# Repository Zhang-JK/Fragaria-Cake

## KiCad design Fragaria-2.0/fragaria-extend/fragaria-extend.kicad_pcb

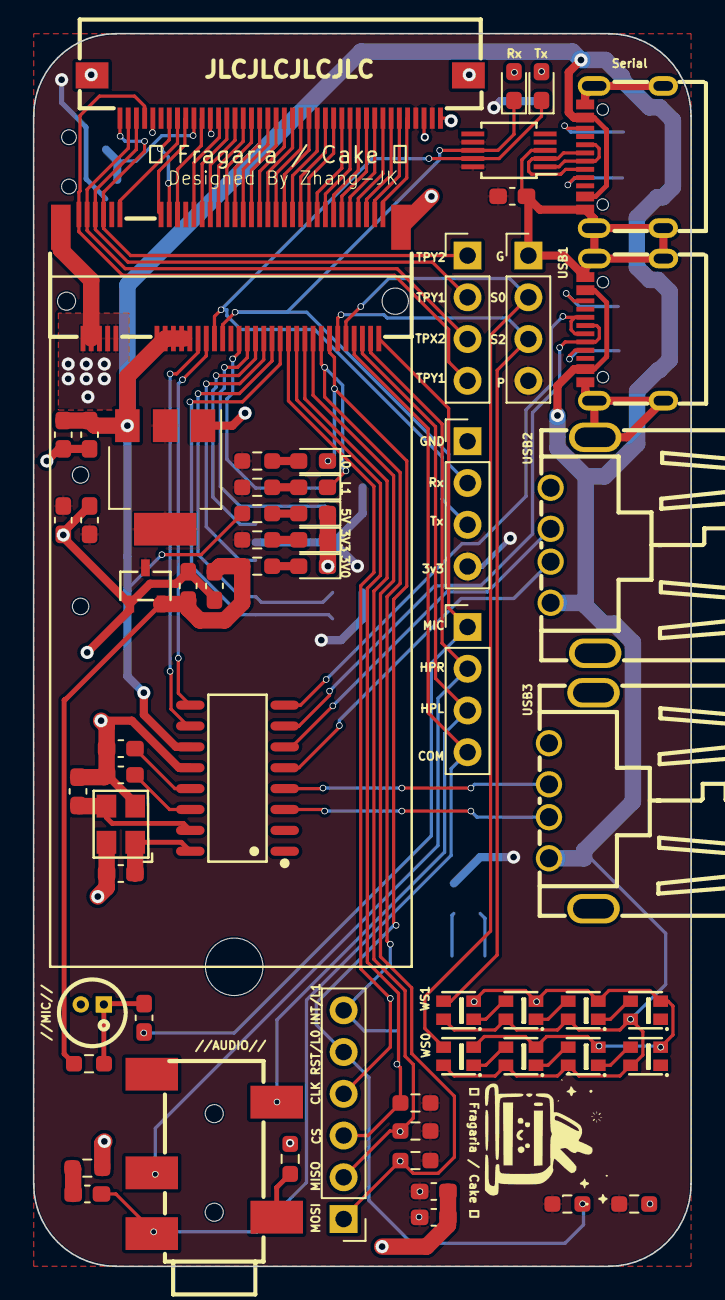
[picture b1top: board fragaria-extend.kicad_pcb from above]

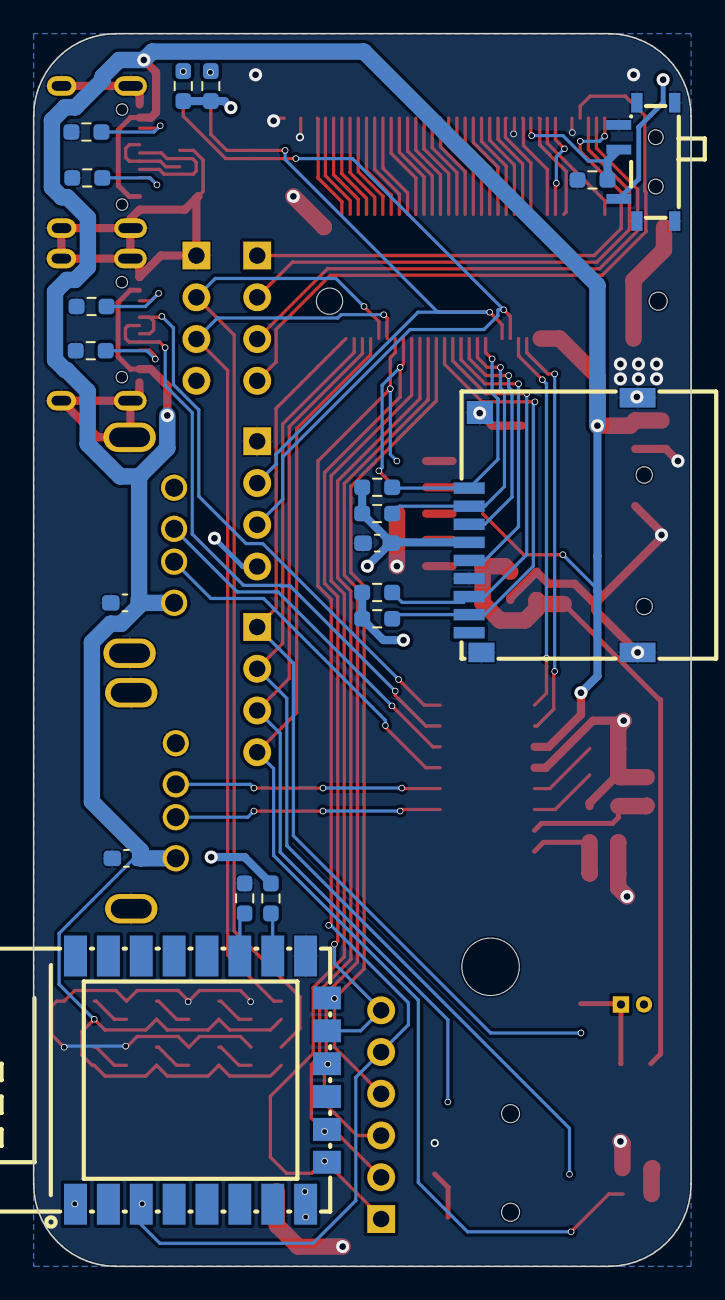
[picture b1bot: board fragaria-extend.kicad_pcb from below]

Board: 2 copper layers, 40.0 x 75.0 mm, 81 parts (19 on the bottom side), 94 nets.

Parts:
C1, C3, C5, C11, C13, C14, C16, C18, C19: 0.1uF; C_0603_1608Metric_Pad1.08x0.95mm_HandSolder
C2, C4, C6, C9, C10, C15: 10uF; C_0603_1608Metric_Pad1.08x0.95mm_HandSolder
C7, C8: 20pF; C_0603_1608Metric_Pad1.08x0.95mm_HandSolder
C17: 2.2uF; C_0603_1608Metric_Pad1.08x0.95mm_HandSolder
CN1: AS0BC21-S40BB-7H; CONN-SMD_AS0BC21-S30BB-7H
CN2: PJ-327A_5JJ; AUDIO-SMD_PJ-327A5JJ
Card1: MR01A-01211; TF-SMD_MR01A-01211
D1, D2, D3, D4: LED-R; LED_0603_1608Metric_Pad1.05x0.95mm_HandSolder
D5: LED-B; LED_0603_1608Metric_Pad1.05x0.95mm_HandSolder
D6, D7: LED-G; LED_0603_1608Metric_Pad1.05x0.95mm_HandSolder
FPC1: AFC01-S40FCA-00; FPC-SMD_P0.50-40P_FGS-XJ-H2.0
J1, J2, J4, J5: Conn_01x04; PinHeader_1x04_P2.54mm_Vertical
J3: Conn_01x06; PinHeader_1x06_P2.54mm_Vertical
LED1, LED2, LED3, LED4, LED5, LED6, LED7, LED8: WS2812B-2020; LED-SMD_4P-L2.0-W2.0-TL_WS2812B-2020
MIC1: B4012AP422-003; MIC-TH_BD4.0-P1.40-D0.3-L
R1, R2, R3, R8, R9, R10, R11: 2kΩ; R_0603_1608Metric_Pad0.98x0.95mm_HandSolder
R4, R5, R6, R7: 5.1kΩ; R_0603_1608Metric_Pad0.98x0.95mm_HandSolder
R12, R13, R14, R15, R16, R23, R24, R25, R26: 10KΩ; R_0603_1608Metric_Pad0.98x0.95mm_HandSolder
R17, R18, R19, R20: 47kΩ; R_0603_1608Metric_Pad0.98x0.95mm_HandSolder
R21: 22Ω; R_0603_1608Metric_Pad0.98x0.95mm_HandSolder
R22: 1KΩ; R_0603_1608Metric_Pad0.98x0.95mm_HandSolder
SW1: MSK12C02; SW-TH_MSK12C02
U1: XC6206P302MR_C347375; SOT-23-3_L3.0-W1.7-P0.95-LS2.9-BR
U2: AMS1117-3.3; SOT-223-3_TabPin2
U3: SL2.1A; SOP-16_L10.0-W3.9-P1.27-LS6.0-BL
U4: CH340E; MSOP-10_3x3mm_P0.5mm
U5: ESP-12F(ESP8266MOD); WIFIM-SMD_ESP-12F-ESP8266MOD
USB1, USB2: TYPE-C_16PIN_2MD(073); USB-C-SMD_TYPE-C-6PIN-2MD-073
USB4, USB5: 292303-1; USB-A-TH_USB-302-T
X1: X322512MSB4SI; OSC-SMD_4P-L3.2-W2.5-BL
locked: locked; MountingHole_3.5mm

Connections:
+3V0: C3.2, C6.2, R3.1, R14.1, U1.2 (VOUT)
+3V3: C4.1, C5.1, C11.2, C15.2, C16.2, C18.2, Card1.4 (VDD), FPC1.2, FPC1.4, J2.4, J5.4, R2.1, R8.1, R9.1, R10.1, R11.1, R12.1, R13.1, R15.1, R17.1, R18.1, R19.1, R20.1, R23.2, R24.2, R25.2, SW1.1, U1.3 (VIN), U2.2 (VO), U4.7 (VCC), U4.10 (V3), U5.8 (VCC)
+5V: C1.1, C2.1, C13.2, C14.2, CN1.20, CN1.22, CN1.24, CN1.26, CN1.28, LED1.4 (VDD), LED2.4 (VDD), LED3.4 (VDD), LED4.4 (VDD), LED5.4 (VDD), LED6.4 (VDD), LED7.4 (VDD), LED8.4 (VDD), R1.1, U2.3 (VI), U3.11 (VDD5), USB1.2 (VBUS), USB1.11 (VBUS), USB2.2 (VBUS), USB2.11 (VBUS), USB4.1 (S+), USB5.1 (S+)
/BD+: CN1.30, U3.10 (DP)
/BD-: CN1.32, U3.9 (DM)
/D+: U4.1 (UD+), USB1.6 (DP1), USB1.8 (DP2)
/D-: U4.2 (UD-), USB1.5 (DN2), USB1.7 (DN1)
/DN1: U3.7 (DM1), USB2.5 (DN2), USB2.7 (DN1)
/DN2: U3.5 (DM2), USB4.2 (D-)
/DN3: U3.3 (DM3), USB5.2 (D-)
/DP1: U3.8 (DP1), USB2.6 (DP1), USB2.8 (DP2)
/DP2: U3.6 (DP2), USB4.3 (D+)
/DP3: U3.4 (DP3), USB5.3 (D+)
/HPCOM: C19.2, CN1.68, CN2.1, J4.4
/HPL: CN1.70, CN2.4, J4.3
/HPR: CN1.72, CN2.3, J4.2
/LCD_CLK: CN1.25, FPC1.30
/LCD_D0: CN1.75, FPC1.5
/LCD_D1: CN1.73, FPC1.6
/LCD_D2: CN1.71, FPC1.7
/LCD_D3: CN1.69, FPC1.8
/LCD_D4: CN1.67, FPC1.9
/LCD_D5: CN1.65, FPC1.10
/LCD_D6: CN1.63, FPC1.11
/LCD_D7: CN1.61, FPC1.12
/LCD_D8: CN1.59, FPC1.13
/LCD_D9: CN1.57, FPC1.14
/LCD_D10: CN1.55, FPC1.15
/LCD_D11: CN1.53, FPC1.16
/LCD_D12: CN1.51, FPC1.17
/LCD_D13: CN1.49, FPC1.18
/LCD_D14: CN1.47, FPC1.19
/LCD_D15: CN1.45, FPC1.20
/LCD_D16: CN1.43, FPC1.21
/LCD_D17: CN1.41, FPC1.22
/LCD_D18: CN1.39, FPC1.23
/LCD_D19: CN1.37, FPC1.24
/LCD_D20: CN1.35, FPC1.25
/LCD_D21: CN1.33, FPC1.26
/LCD_D22: CN1.31, FPC1.27
/LCD_D23: CN1.29, FPC1.28
/LCD_DE: CN1.23, FPC1.34
/LCD_EN: FPC1.31, R26.1, SW1.2
/LCD_HSYNC: CN1.21, FPC1.32
/LCD_VSYNC: CN1.11, FPC1.33
/LED0: CN1.62, D4.1 (K), J3.5, R13.2, U5.3 (EN)
/LED1: CN1.60, D6.1 (K), J3.6, U5.21 (MOSI)
/MICIN: C17.2, CN1.74, J4.1
/SD_CLK: CN1.46, Card1.5 (CLK)
/SD_CMD: CN1.44, Card1.3 (CMD)
/SD_D0: CN1.48, Card1.7 (DAT0), R19.2
/SD_D1: CN1.50, Card1.8 (DAT1), R20.2
/SD_D2: CN1.40, Card1.1 (DAT2), R17.2
/SD_D3: CN1.42, Card1.2 (CD/DAT3), R18.2
/SPI0_CLK: CN1.52, J3.4, U5.22 (SCLK)
/SPI0_CS: CN1.54, J3.3, R23.1, U5.20 (GPIO10)
/SPI0_MISO: CN1.56, J3.2, R24.1, U5.18 (MISO)
/SPI0_MOSI: CN1.58, J3.1, R25.1, U5.17 (CS0)
/TPX1: CN1.1, FPC1.37, J1.4
/TPX2: CN1.3, FPC1.39, J1.3
/TPY1: CN1.5, FPC1.38, J1.2
/TPY2: CN1.7, FPC1.40, J1.1
/U2_RX: CN1.36, D5.1 (K), J2.2, U4.8 (TXD)
/U2_TX: CN1.34, D7.1 (K), J2.3, U4.9 (RXD)
/WS0: CN1.66, J5.2, LED2.3 (DI)
/WS1: CN1.64, J5.3, LED1.3 (DI)
/XIN: C8.2, U3.16 (XIN), X1.1 (OSC1)
/XOUT: C7.1, U3.15 (XOUT), X1.3 (OSC2)
GND: C1.2, C2.2, C3.1, C4.2, C5.2, C6.1, C7.2, C8.1, C9.2, C10.2, C11.1, C13.1, C14.1, C15.1, C16.1, C18.1, CN1.2, CN1.4, CN1.6, CN1.8, CN1.10, CN1.76, CN1.77, Card1.6 (VSS), Card1.10 (GND), Card1.11 (GND), Card1.12 (GND), Card1.13 (GND), D1.1 (K), D2.1 (K), D3.1 (K), FPC1.1, FPC1.3, FPC1.29, FPC1.36, FPC1.41, FPC1.42, J2.1, J5.1, LED1.2 (GND), LED2.2 (GND), LED3.2 (GND), LED4.2 (GND), LED5.2 (GND), LED6.2 (GND), LED7.2 (GND), LED8.2 (GND), MIC1.2 (GND), R4.2, R5.2, R6.2, R7.2, R16.1, R21.1, R22.2, R26.2, SW1.3, SW1.4, U1.1 (VSS), U2.1 (GND), U3.12 (GND), U4.3 (GND), U5.9 (GND), USB1.1 (GND), USB1.12 (GND), USB1.13 (SHELL), USB1.14 (SHELL), USB2.1 (GND), USB2.12 (GND), USB2.13 (SHELL), USB2.14 (SHELL), USB4.4 (S-), USB4.5, USB4.6, USB5.4 (S-), USB5.5, USB5.6, X1.2 (GND), X1.4 (GND)
unnamed: C19.1, R21.2
unnamed: CN2.2, R22.1
unnamed: D1.2 (A), R1.2
unnamed: D2.2 (A), R2.2
unnamed: D3.2 (A), R3.2
unnamed: D4.2 (A), R8.2
unnamed: D5.2 (A), R9.2
unnamed: D6.2 (A), R10.2
unnamed: D7.2 (A), R11.2
unnamed: LED1.1 (DO), LED3.3 (DI)
unnamed: LED2.1 (DO), LED4.3 (DI)
unnamed: LED3.1 (DO), LED5.3 (DI)
unnamed: LED4.1 (DO), LED6.3 (DI)
unnamed: LED5.1 (DO), LED7.3 (DI)
unnamed: LED6.1 (DO), LED8.3 (DI)
unnamed: C17.1, MIC1.1 (OUT), R14.2
unnamed: C10.1, U3.14 (VDD18)
unnamed: C9.1, U3.13 (VDD33)
unnamed: R16.2, U5.11 (GPIO2)
unnamed: R15.2, U5.10 (GPIO15)
unnamed: R12.2, U5.1 (RST)
unnamed: R5.1, USB1.4 (CC1)
unnamed: R4.1, USB1.10 (CC2)
unnamed: R7.1, USB2.4 (CC1)
unnamed: R6.1, USB2.10 (CC2)

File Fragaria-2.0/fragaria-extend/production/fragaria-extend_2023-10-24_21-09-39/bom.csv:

Designator,Footprint,Quantity,Value,LCSC Part #
"C1, C13, C14, C16, C19, C5",0603,6,100nF,
"C10, C15, C2, C4, C6, C9",0603,6,10uF,
"C11, C18, C3",0603,3,0.1uF,
C17,0603,1,2.2uF,
"C7, C8",0603,2,20pF,
CN1,CONN-SMD_AS0BC21-S30BB-7H,1,AS0BC21-S40BB-7H,
CN2,AUDIO-SMD_PJ-327A5JJ,1,PJ-327A_5JJ,
Card1,TF-SMD_MR01A-01211,1,MR01A-01211,
"D1, D2, D3, D4",0603,4,LED-R,
D5,0603,1,LED-B,
"D6, D7",0603,2,LED-G,
FPC1,FPC-SMD_P0.50-40P_FGS-XJ-H2.0,1,AFC01-S40FCA-00,
H1,MountingHole_3.5mm,1,MountingHole,
"J1, J2, J4, J5",PinHeader_1x04_P2.54mm_Vertical,4,Conn_01x04,
J3,PinHeader_1x06_P2.54mm_Vertical,1,Conn_01x06,
"LED1, LED2, LED3, LED4, LED5, LED6, LED7, LED8",LED-SMD_4P-L2.0-W2.0-TL_WS2812B-2020,8,WS2812B-2020,
MIC1,MIC-TH_BD4.0-P1.40-D0.3-L,1,B4012AP422-003,
"R1, R10, R11, R2, R3, R8, R9",0603,7,2kΩ,
"R12, R13, R14, R15, R16, R23, R24, R25, R26",0603,9,10KΩ,
"R17, R18, R19, R20",0603,4,47kΩ,
R21,0603,1,22Ω,
R22,0603,1,1KΩ,
"R4, R5, R6, R7",0603,4,5.1kΩ,
SW1,SW-TH_MSK12C02,1,MSK12C02,
U1,SOT-23-3_L3.0-W1.7-P0.95-LS2.9-BR,1,XC6206P302MR_C347375,
U2,SOT-223-3_TabPin2,1,AMS1117-3.3,
U3,SOP-16_L10.0-W3.9-P1.27-LS6.0-BL,1,SL2.1A,
U4,MSOP-10_3x3mm_P0.5mm,1,CH340E,
U5,WIFIM-SMD_ESP-12F-ESP8266MOD,1,ESP-12F(ESP8266MOD),
"USB1, USB2",USB-C-SMD_TYPE-C-6PIN-2MD-073,2,TYPE-C_16PIN_2MD(073),
"USB4, USB5",USB-A-TH_USB-302-T,2,292303-1,
X1,OSC-SMD_4P-L3.2-W2.5-BL,1,X322512MSB4SI,

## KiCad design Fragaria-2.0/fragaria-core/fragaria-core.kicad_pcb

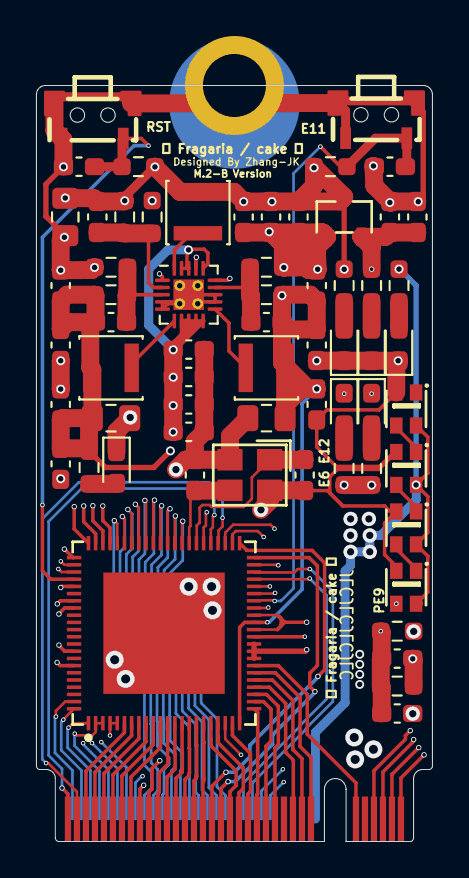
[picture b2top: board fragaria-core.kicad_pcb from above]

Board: 4 copper layers, 22.0 x 42.0 mm, 64 parts (0 on the bottom side), 80 nets.

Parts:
111: M.2-B-KEY
C1, C2, C8, C10, C12, C13, C17, C18, C19, C20, C26, C27, C28: 0.1uF; C_0603_1608Metric_Pad1.08x0.95mm_HandSolder
C3, C4: 18pF; C_0603_1608Metric_Pad1.08x0.95mm_HandSolder
C5, C6, C7: 10uF; C_0805_2012Metric_Pad1.18x1.45mm_HandSolder
C9, C21, C22, C23, C24: 10uF; C_0603_1608Metric_Pad1.08x0.95mm_HandSolder
C11, C25: 1uF; C_0603_1608Metric_Pad1.08x0.95mm_HandSolder
C14, C15, C16: 220pF; C_0603_1608Metric_Pad1.08x0.95mm_HandSolder
D1, D3, D4, D5, D6: LED-R; LED_0603_1608Metric_Pad1.05x0.95mm_HandSolder
D2: LED-G; LED_0603_1608Metric_Pad1.05x0.95mm_HandSolder
L1, L2, L3: 2.2uH; L_Changjiang_FNR3015S
LED1, LED2, LED3, LED4: WS2812B-2020; LED-SMD_4P-L2.0-W2.0-TL_WS2812B-2020
R1, R2, R8, R12, R13, R14, R15, R16: 2kΩ; R_0603_1608Metric_Pad0.98x0.95mm_HandSolder
R3, R4: 10kΩ; R_0603_1608Metric_Pad0.98x0.95mm_HandSolder
R5, R6, R7: 150kΩ; R_0603_1608Metric_Pad0.98x0.95mm_HandSolder
R9: 130kΩ; R_0603_1608Metric_Pad0.98x0.95mm_HandSolder
R10: 470kΩ; R_0603_1608Metric_Pad0.98x0.95mm_HandSolder
R11: 680kΩ; R_0603_1608Metric_Pad0.98x0.95mm_HandSolder
SW1, SW2: DS-THAM04-ABB-R; SW-SMD_D-SWITCH_DS-THAM04-ABB-R
U1: F1C200S; QFN-88_L10.0-W10.0-P0.40-BL-EP6.75
U2: XC6206P302MR_C347375; SOT-23-3_L3.0-W1.7-P0.95-LS2.9-BR
U3: EA3036C; WQFN-20-1EP_3x3mm_P0.4mm_EP1.7x1.7mm_ThermalVias
X1: SMD-3225_4P_24.000MHZ_18PF; CRYSTAL-SMD_4P-L3.2-W2.5-BL

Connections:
+1V1: C5.1, C10.1, C12.1, C14.1, C18.1, L1.1, R9.1, U1.22 (VDD-CORE), U1.35 (VDD-CORE), U1.71 (VDD-CORE)
+2V5: C6.1, C9.1, C11.1, C13.1, C15.1, C17.1, C19.1, L2.1, R10.1, R12.1, R16.1, U1.30 (VCC-DRAM), U1.31 (VCC-DRAM), U1.32 (VCC-DRAM), U1.34 (VCC-DRAM), U1.36 (VCC-DRAM)
+3V0: C20.2, C21.2, R15.1, U1.80 (AVCC), U2.2 (VOUT)
+3V3: C7.1, C16.1, C26.1, C27.1, C28.1, L3.1, R1.1, R2.1, R3.2, R4.2, R11.1, R14.1, U1.4 (HPVCC), U1.5 (VCC-IO), U1.20 (VCC-IO), U1.50 (VCC-IO), U1.67 (UVCC), U1.73 (TV_VCC), U2.3 (VIN)
+5V: 111.P$20 (20), 111.P$22 (22), 111.P$24 (24), 111.P$26 (26), 111.P$28 (28), C22.1, C23.1, C24.1, C25.1, LED1.4 (VDD), LED2.4 (VDD), LED3.4 (VDD), LED4.4 (VDD), R13.1, U3.7 (VIN2), U3.8 (EN2), U3.9 (EN1), U3.10 (VIN1), U3.16 (VCC), U3.18 (EN3), U3.19 (VIN3)
/BD+: 111.P$30 (30), U1.69 (USB-DP)
/BD-: 111.P$32 (32), U1.68 (USB-DM)
/HOSCI: C3.2, U1.51 (HOSCI), X1.1 (OSC1)
/HOSCO: C4.1, U1.52 (HOSCO), X1.3 (OSC2)
/HPCOM: 111.P$68 (68), U1.2 (HIPCOMFB), U1.3 (HPCOM)
/HPL: 111.P$70 (70), U1.1 (HPL)
/HPR: 111.P$72 (72), U1.88 (HPR)
/LCD_CLK: 111.P$25 (25), U1.26 (PD18)
/LCD_D0: 111.P$75 (75), U1.49 (PE0)
/LCD_D1: 111.P$73 (73), U1.48 (PE1)
/LCD_D2: 111.P$71 (71), U1.6 (PD0)
/LCD_D3: 111.P$69 (69), U1.7 (PD1)
/LCD_D4: 111.P$67 (67), U1.8 (PD2)
/LCD_D5: 111.P$65 (65), U1.9 (PD3)
/LCD_D6: 111.P$63 (63), U1.10 (PD4)
/LCD_D7: 111.P$61 (61), U1.11 (PD5)
/LCD_D8: 111.P$59 (59), U1.47 (PE2)
/LCD_D9: 111.P$57 (57), U1.46 (PE3)
/LCD_D10: 111.P$55 (55), U1.12 (PD6)
/LCD_D11: 111.P$53 (53), U1.13 (PD7)
/LCD_D12: 111.P$51 (51), U1.14 (PD8)
/LCD_D13: 111.P$49 (49), U1.15 (PD9)
/LCD_D14: 111.P$47 (47), U1.16 (PD10)
/LCD_D15: 111.P$45 (45), U1.17 (PD11)
/LCD_D16: 111.P$43 (43), U1.45 (PE4)
/LCD_D17: 111.P$41 (41), U1.44 (PE5)
/LCD_D18: 111.P$39 (39), U1.18 (PD12)
/LCD_D19: 111.P$37 (37), U1.19 (PD13)
/LCD_D20: 111.P$35 (35), U1.21 (PD14)
/LCD_D21: 111.P$33 (33), U1.23 (PD15)
/LCD_D22: 111.P$31 (31), U1.24 (PD16)
/LCD_D23: 111.P$29 (29), U1.25 (PD17)
/LCD_DE: 111.P$23 (23), U1.27 (PD19)
/LCD_HSYNC: 111.P$21 (21), U1.28 (PD20)
/LCD_VSYNC: 111.P$11 (11), U1.29 (PD21)
/LED0: 111.P$62 (62), D1.1 (K), U1.37 (PE12)
/LED1: 111.P$60 (60), D2.1 (K), U1.43 (PE6)
/MICIN: 111.P$74 (74), U1.87 (MICIN)
/REF_DRAM: C8.1, C13.2, R8.1, R12.2, U1.33 (SVREF)
/RESET: C1.2, R3.1, SW1.2, U1.70 (RESET)
/SD_CLK: 111.P$46 (46), U1.56 (PF2)
/SD_CMD: 111.P$44 (44), U1.55 (PF3)
/SD_D0: 111.P$48 (48), U1.57 (PF1)
/SD_D1: 111.P$50 (50), U1.58 (PF0)
/SD_D2: 111.P$40 (40), U1.53 (PF5)
/SD_D3: 111.P$42 (42), U1.54 (PF4)
/SPI0_CLK: 111.P$52 (52), U1.59 (PC0)
/SPI0_CS: 111.P$54 (54), U1.60 (PC1)
/SPI0_MISO: 111.P$56 (56), U1.61 (PC2)
/SPI0_MOSI: 111.P$58 (58), U1.62 (PC3)
/SW0: C2.2, R4.1, SW2.2, U1.38 (PE11)
/TPX1: 111.P$1 (1), U1.66 (TPX1)
/TPX2: 111.P$3 (3), U1.65 (TPX2)
/TPY1: 111.P$5 (5), U1.64 (TPY1)
/TPY2: 111.P$7 (7), U1.63 (TPY2)
/U2_RX: 111.P$36 (36), U1.41 (PE8)
/U2_TX: 111.P$34 (34), U1.42 (PE7)
/WS0: 111.P$66 (66), LED4.3 (DI), U1.40 (PE9)
/WS1: 111.P$64 (64), U1.39 (PE10)
GND: 111.MOUNTING-HOLE (MP1), 111.P$2 (2), 111.P$4 (4), 111.P$6 (6), 111.P$8 (8), 111.P$10 (10), C1.1, C2.1, C3.1, C4.2, C5.2, C6.2, C7.2, C8.2, C9.2, C10.2, C11.2, C12.2, C17.2, C18.2, C19.2, C20.1, C21.1, C22.2, C23.2, C24.2, C25.2, C26.2, C27.2, C28.2, D3.1 (K), D4.1 (K), D5.1 (K), D6.1 (K), LED1.2 (GND), LED2.2 (GND), LED3.2 (GND), LED4.2 (GND), R5.1, R6.1, R7.1, R8.2, SW1.1, SW1.3, SW1.4, SW2.1, SW2.3, SW2.4, U1.74 (TVGND), U1.82 (AGND), U1.89 (GND), U2.1 (VSS), U3.1 (GND3), U3.4 (GND2), U3.5 (GND2), U3.12 (GND1), U3.13 (GND1), U3.15 (AGND), U3.17 (AGND), U3.21 (PAD), X1.2 (GND), X1.4 (GND)
unnamed: D1.2 (A), R1.2
unnamed: D2.2 (A), R2.2
unnamed: D3.2 (A), R13.2
unnamed: D4.2 (A), R14.2
unnamed: D5.2 (A), R15.2
unnamed: D6.2 (A), R16.2
unnamed: LED1.3 (DI), LED2.1 (DO)
unnamed: LED2.3 (DI), LED3.1 (DO)
unnamed: LED3.3 (DI), LED4.1 (DO)
unnamed: C14.2, R5.2, R9.2, U3.14 (FB1)
unnamed: C15.2, R6.2, R10.2, U3.3 (FB2)
unnamed: C16.2, R7.2, R11.2, U3.2 (FB3)
unnamed: L1.2, U3.11 (LX1)
unnamed: L2.2, U3.6 (LX2)
unnamed: L3.2, U3.20 (LX3)

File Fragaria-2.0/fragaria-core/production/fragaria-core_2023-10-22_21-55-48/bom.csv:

Designator,Footprint,Quantity,Value,LCSC Part #
111,M.2-B-KEY,1,M.2-B-KEY,
"C1, C10, C12, C13, C17, C18, C19, C2, C20, C26, C27, C28, C8",0603,13,0.1uF,
"C11, C25",0603,2,1uF,
"C14, C15, C16",0603,3,220pF,
"C21, C22, C23, C24, C9",0603,5,10uF,
"C3, C4",0603,2,18pF,
"C5, C6, C7",0805,3,10uF,
"D1, D3, D4, D5, D6",0603,5,LED-R,
D2,0603,1,LED-G,
"L1, L2, L3",L_Changjiang_FNR3015S,3,2.2uH,
"LED1, LED2, LED3, LED4",LED-SMD_4P-L2.0-W2.0-TL_WS2812B-2020,4,WS2812B-2020,
"R1, R12, R13, R14, R15, R16, R2, R8",0603,8,2kΩ,
R10,0603,1,470kΩ,
R11,0603,1,680kΩ,
"R3, R4",0603,2,10kΩ,
"R5, R6, R7",0603,3,150kΩ,
R9,0603,1,130kΩ,
"SW1, SW2",SW-SMD_D-SWITCH_DS-THAM04-ABB-R,2,DS-THAM04-ABB-R,
U1,QFN-88_L10.0-W10.0-P0.40-BL-EP6.75,1,F1C200S,
U2,SOT-23-3_L3.0-W1.7-P0.95-LS2.9-BR,1,XC6206P302MR_C347375,
U3,WQFN-20-1EP_3x3mm_P0.4mm_EP1.7x1.7mm_ThermalVias,1,EA3036C,
X1,CRYSTAL-SMD_4P-L3.2-W2.5-BL,1,SMD-3225_4P_24.000MHZ_18PF,

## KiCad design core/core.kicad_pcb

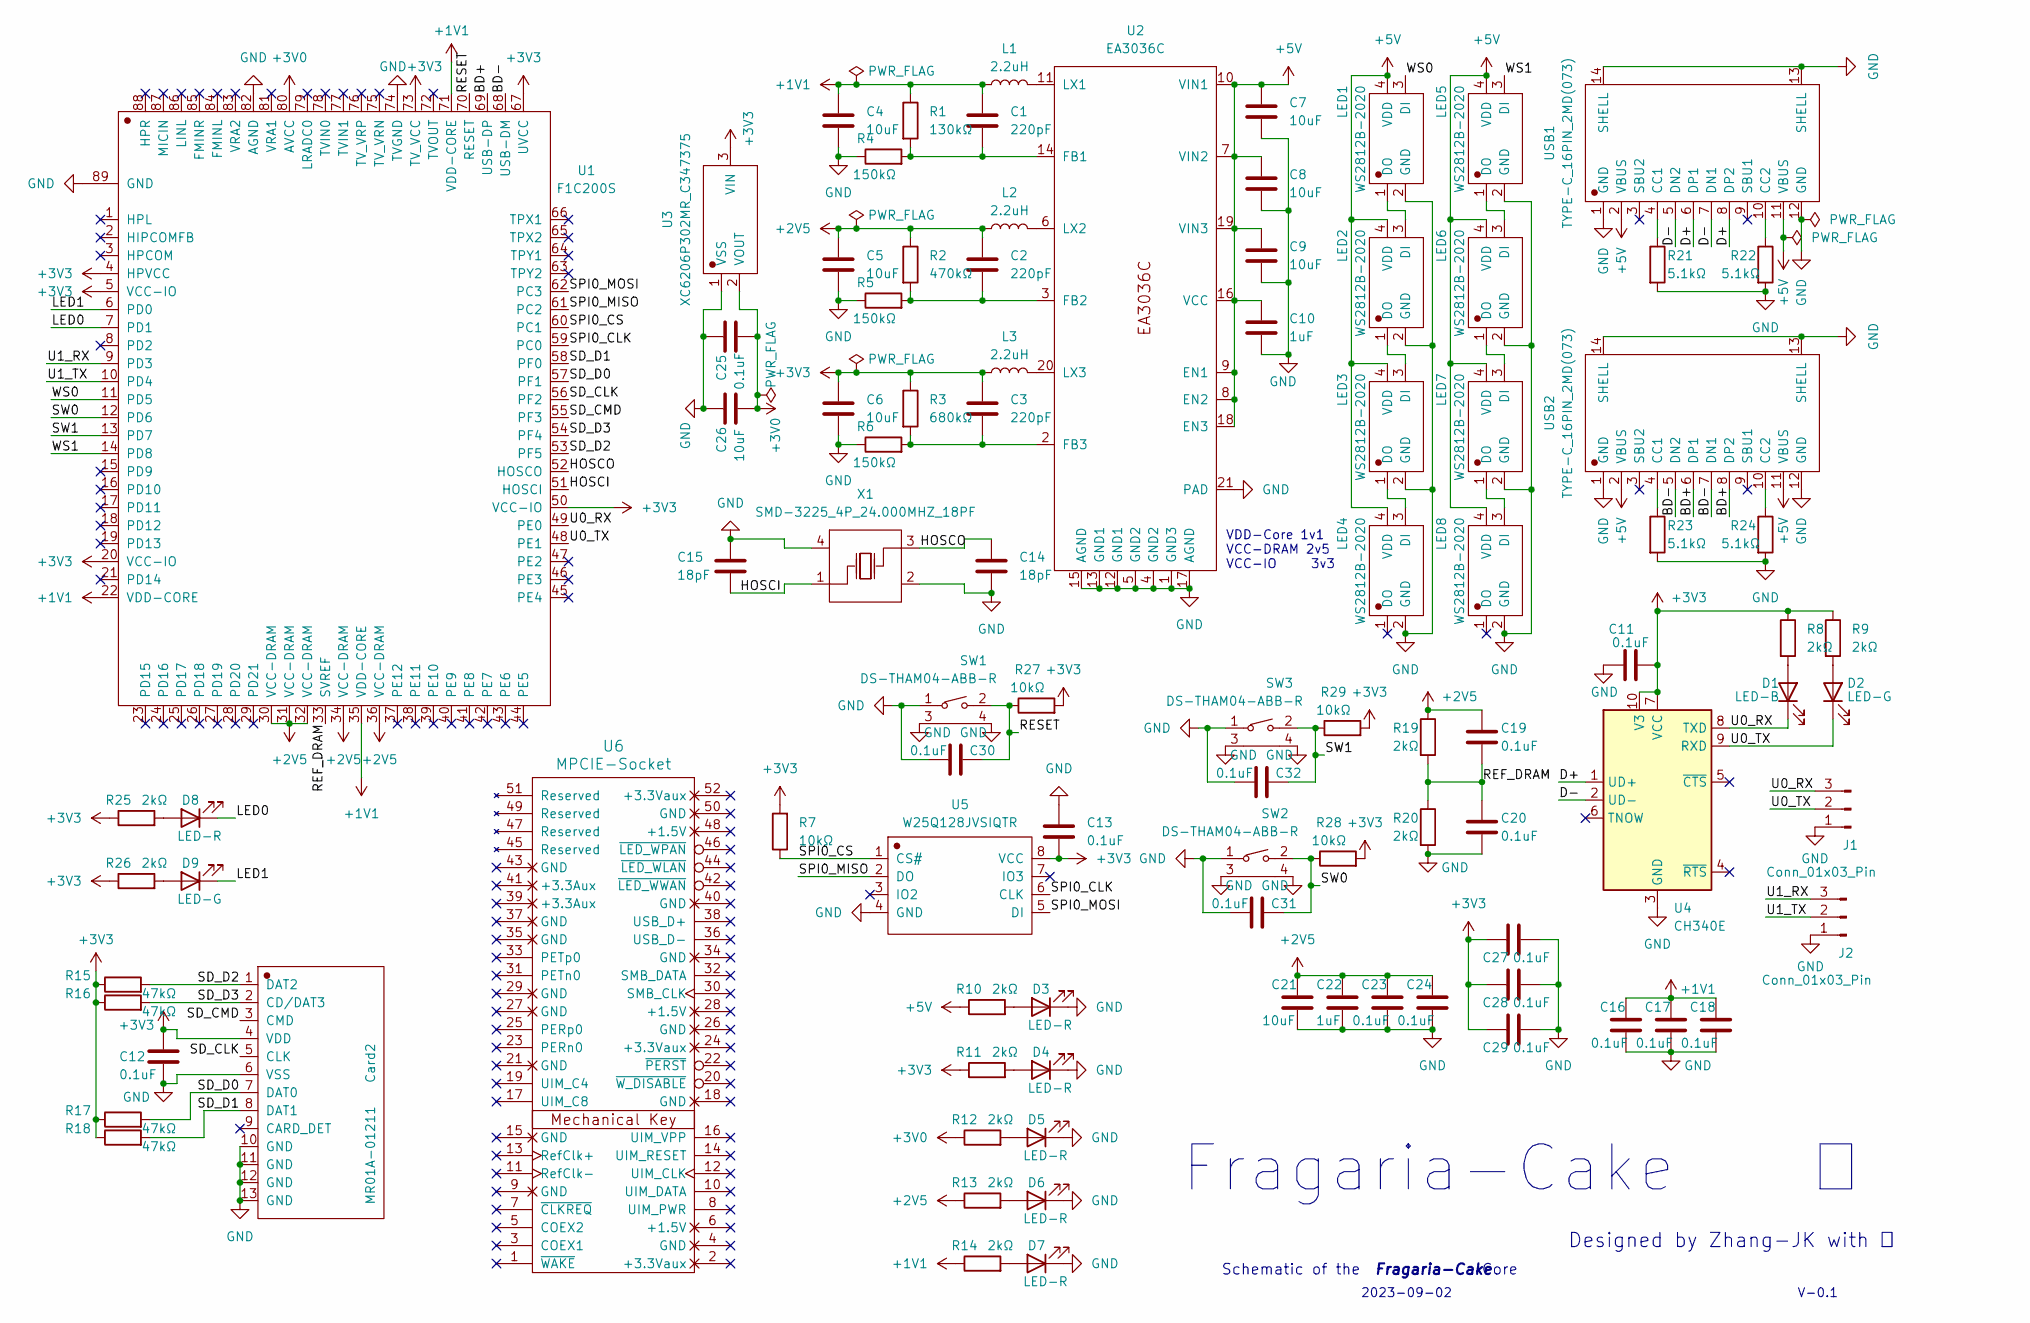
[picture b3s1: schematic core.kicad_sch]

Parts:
C1, C2, C3: 220pF; C_0603_1608Metric_Pad1.08x0.95mm_HandSolder
C4, C5, C6: 10uF; C_0805_2012Metric_Pad1.18x1.45mm_HandSolder
C7, C8, C9, C21, C26: 10uF; C_0603_1608Metric_Pad1.08x0.95mm_HandSolder
C10, C22: 1uF; C_0603_1608Metric_Pad1.08x0.95mm_HandSolder
C11, C12, C13, C16, C17, C18, C19, C20, C23, C24, C25, C27, C28, C29, C30, C31, C32: 0.1uF; C_0603_1608Metric_Pad1.08x0.95mm_HandSolder
C14, C15: 18pF; C_0603_1608Metric_Pad1.08x0.95mm_HandSolder
Card2: MR01A-01211; TF-SMD_MR01A-01211
D1: LED-B; LED_0603_1608Metric_Pad1.05x0.95mm_HandSolder
D2, D9: LED-G; LED_0603_1608Metric_Pad1.05x0.95mm_HandSolder
D3, D4, D5, D6, D7, D8: LED-R; LED_0603_1608Metric_Pad1.05x0.95mm_HandSolder
J1, J2: Conn_01x03_Pin; PinHeader_1x03_P1.27mm_Vertical
L1, L2, L3: 2.2uH; L_Changjiang_FNR3015S
LED1, LED2, LED3, LED4, LED5, LED6, LED7, LED8: WS2812B-2020; LED-SMD_4P-L2.0-W2.0-TL_WS2812B-2020
R1: 130kΩ; R_0603_1608Metric_Pad0.98x0.95mm_HandSolder
R2: 470kΩ; R_0603_1608Metric_Pad0.98x0.95mm_HandSolder
R3: 680kΩ; R_0603_1608Metric_Pad0.98x0.95mm_HandSolder
R4, R5, R6: 150kΩ; R_0603_1608Metric_Pad0.98x0.95mm_HandSolder
R7, R27, R28, R29: 10kΩ; R_0603_1608Metric_Pad0.98x0.95mm_HandSolder
R8, R9, R10, R11, R12, R13, R14, R19, R20, R25, R26: 2kΩ; R_0603_1608Metric_Pad0.98x0.95mm_HandSolder
R15, R16, R17, R18: 47kΩ; R_0603_1608Metric_Pad0.98x0.95mm_HandSolder
R21, R22, R23, R24: 5.1kΩ; R_0603_1608Metric_Pad0.98x0.95mm_HandSolder
SW1, SW2, SW3: DS-THAM04-ABB-R; SW-SMD_D-SWITCH_DS-THAM04-ABB-R
U1: F1C200S; QFN-88_L10.0-W10.0-P0.40-BL-EP6.75
U2: EA3036C; WQFN-20_L3.0-W3.0-P0.40-BL-EP
U3: XC6206P302MR_C347375; SOT-23-3_L3.0-W1.7-P0.95-LS2.9-BR
U4: CH340E; MSOP-10_3x3mm_P0.5mm
U5: W25Q128JVSIQTR; SOIC-8_L5.3-W5.3-P1.27-LS8.0-BL
U6: MPCIE-Socket; mpcie-full-card
USB1, USB2: TYPE-C_16PIN_2MD(073); USB-C-SMD_TYPE-C-6PIN-2MD-073
X1: SMD-3225_4P_24.000MHZ_18PF; CRYSTAL-SMD_4P-L3.2-W2.5-BL

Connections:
+1V1: C1.1, C4.1, C16.1, C17.1, C18.1, L1.1, R1.1, R14.1, U1.22 (VDD-CORE), U1.35 (VDD-CORE), U1.71 (VDD-CORE)
+2V5: C2.1, C5.1, C19.1, C21.1, C22.1, C23.1, C24.1, L2.1, R2.1, R13.1, R19.1, U1.30 (VCC-DRAM), U1.31 (VCC-DRAM), U1.32 (VCC-DRAM), U1.34 (VCC-DRAM), U1.36 (VCC-DRAM)
+3V0: C25.2, C26.2, R12.1, U1.80 (AVCC), U3.2 (VOUT)
+3V3: C3.1, C6.1, C11.2, C12.2, C13.2, C27.1, C28.1, C29.1, Card2.4 (VDD), L3.1, R3.1, R7.2, R8.1, R9.1, R11.1, R15.1, R16.1, R17.1, R18.1, R25.1, R26.1, R27.2, R28.2, R29.2, U1.4 (HPVCC), U1.5 (VCC-IO), U1.20 (VCC-IO), U1.50 (VCC-IO), U1.67 (UVCC), U1.73 (TV_VCC), U3.3 (VIN), U4.7 (VCC), U4.10 (V3), U5.8 (VCC)
+5V: C7.1, C8.1, C9.1, C10.1, LED1.4 (VDD), LED2.4 (VDD), LED3.4 (VDD), LED4.4 (VDD), LED5.4 (VDD), LED6.4 (VDD), LED7.4 (VDD), LED8.4 (VDD), R10.1, U2.7 (VIN2), U2.8 (EN2), U2.9 (EN1), U2.10 (VIN1), U2.16 (VCC), U2.18 (EN3), U2.19 (VIN3), USB1.2 (VBUS), USB1.11 (VBUS), USB2.2 (VBUS), USB2.11 (VBUS)
/BD+: U1.69 (USB-DP), USB2.6 (DP1), USB2.8 (DP2)
/BD-: U1.68 (USB-DM), USB2.5 (DN2), USB2.7 (DN1)
/D+: U4.1 (UD+), USB1.6 (DP1), USB1.8 (DP2)
/D-: U4.2 (UD-), USB1.5 (DN2), USB1.7 (DN1)
/HOSCI: C15.2, U1.51 (HOSCI), X1.1 (OSC1)
/HOSCO: C14.1, U1.52 (HOSCO), X1.3 (OSC2)
/LED0: D8.1 (K), U1.7 (PD1)
/LED1: D9.1 (K), U1.6 (PD0)
/REF_DRAM: C19.2, C20.1, R19.2, R20.1, U1.33 (SVREF)
/RESET: C30.2, R27.1, SW1.2, U1.70 (RESET)
/SD_CLK: Card2.5 (CLK), U1.56 (PF2)
/SD_CMD: Card2.3 (CMD), U1.55 (PF3)
/SD_D0: Card2.7 (DAT0), R17.2, U1.57 (PF1)
/SD_D1: Card2.8 (DAT1), R18.2, U1.58 (PF0)
/SD_D2: Card2.1 (DAT2), R15.2, U1.53 (PF5)
/SD_D3: Card2.2 (CD/DAT3), R16.2, U1.54 (PF4)
/SPI0_CLK: U1.59 (PC0), U5.6 (CLK)
/SPI0_CS: R7.1, U1.60 (PC1), U5.1 (CS#)
/SPI0_MISO: U1.61 (PC2), U5.2 (DO)
/SPI0_MOSI: U1.62 (PC3), U5.5 (DI)
/SW0: C31.2, R28.1, SW2.2, U1.12 (PD6)
/SW1: C32.2, R29.1, SW3.2, U1.13 (PD7)
/U0_RX: D1.1 (K), J1.3, U1.49 (PE0), U4.8 (TXD)
/U0_TX: D2.1 (K), J1.2, U1.48 (PE1), U4.9 (RXD)
/U1_RX: J2.3, U1.9 (PD3)
/U1_TX: J2.2, U1.10 (PD4)
/WS0: LED1.3 (DI), U1.11 (PD5)
/WS1: LED5.3 (DI), U1.14 (PD8)
GND: C4.2, C5.2, C6.2, C7.2, C8.2, C9.2, C10.2, C11.1, C12.1, C13.1, C14.2, C15.1, C16.2, C17.2, C18.2, C20.2, C21.2, C22.2, C23.2, C24.2, C25.1, C26.1, C27.2, C28.2, C29.2, C30.1, C31.1, C32.1, Card2.6 (VSS), Card2.10 (GND), Card2.11 (GND), Card2.12 (GND), Card2.13 (GND), D3.1 (K), D4.1 (K), D5.1 (K), D6.1 (K), D7.1 (K), J1.1, J2.1, LED1.2 (GND), LED2.2 (GND), LED3.2 (GND), LED4.2 (GND), LED5.2 (GND), LED6.2 (GND), LED7.2 (GND), LED8.2 (GND), R4.1, R5.1, R6.1, R20.2, R21.2, R22.2, R23.2, R24.2, SW1.1, SW1.3, SW1.4, SW2.1, SW2.3, SW2.4, SW3.1, SW3.3, SW3.4, U1.74 (TVGND), U1.82 (AGND), U1.89 (GND), U2.1 (GND3), U2.4 (GND2), U2.5 (GND2), U2.12 (GND1), U2.13 (GND1), U2.15 (AGND), U2.17 (AGND), U2.21 (PAD), U3.1 (VSS), U4.3 (GND), U5.4 (GND), USB1.1 (GND), USB1.12 (GND), USB1.13 (SHELL), USB1.14 (SHELL), USB2.1 (GND), USB2.12 (GND), USB2.13 (SHELL), USB2.14 (SHELL), X1.2 (GND), X1.4 (GND)
unnamed: D1.2 (A), R8.2
unnamed: D2.2 (A), R9.2
unnamed: D3.2 (A), R10.2
unnamed: D4.2 (A), R11.2
unnamed: D5.2 (A), R12.2
unnamed: D6.2 (A), R13.2
unnamed: D7.2 (A), R14.2
unnamed: D8.2 (A), R25.2
unnamed: D9.2 (A), R26.2
unnamed: LED1.1 (DO), LED2.3 (DI)
unnamed: LED2.1 (DO), LED3.3 (DI)
unnamed: LED3.1 (DO), LED4.3 (DI)
unnamed: LED5.1 (DO), LED6.3 (DI)
unnamed: LED6.1 (DO), LED7.3 (DI)
unnamed: LED7.1 (DO), LED8.3 (DI)
unnamed: C1.2, R1.2, R4.2, U2.14 (FB1)
unnamed: C2.2, R2.2, R5.2, U2.3 (FB2)
unnamed: C3.2, R3.2, R6.2, U2.2 (FB3)
unnamed: L1.2, U2.11 (LX1)
unnamed: L2.2, U2.6 (LX2)
unnamed: L3.2, U2.20 (LX3)
unnamed: R21.1, USB1.4 (CC1)
unnamed: R22.1, USB1.10 (CC2)
unnamed: R23.1, USB2.4 (CC1)
unnamed: R24.1, USB2.10 (CC2)

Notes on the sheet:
Fragaria-Cake 
Fragaria-Cake
Schematic of the Core
Designed by Zhang-JK with 󱢠
VDD-Core 1v1 VCC-DRAM 2v5 VCC-IO 3v3
V-0.1
2023-09-02

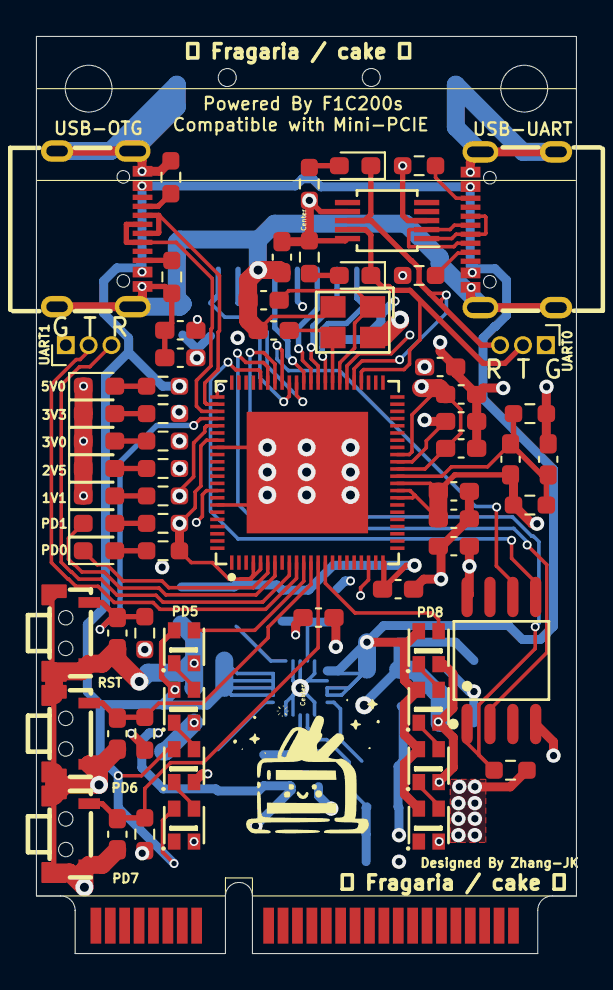
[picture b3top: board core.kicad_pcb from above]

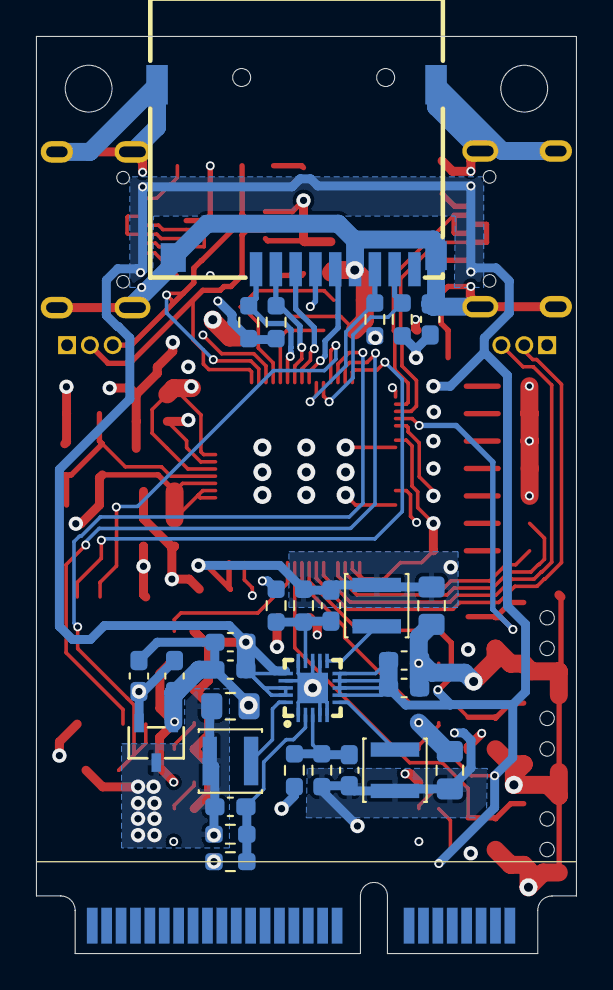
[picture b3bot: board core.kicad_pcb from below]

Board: 4 copper layers, 30.0 x 50.9 mm, 96 parts (29 on the bottom side), 59 nets.

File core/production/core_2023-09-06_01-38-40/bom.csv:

Designator,Footprint,Quantity,Value,LCSC Part #
"C1, C2, C3",0603,3,220pF,
"C10, C22",0603,2,1uF,
"C11, C12, C13, C16, C17, C18, C23, C24, C25, C27, C28, C29, C30, C31, C32",0603,15,0.1uF,
"C14, C15",0603,2,18pF,
"C19, C20",0603,2,0.1nF,
"C21, C26, C7, C8, C9",0603,5,10uF,
"C4, C5, C6",0805,3,10uF,
Card2,TF-SMD_MR01A-01211,1,MR01A-01211,
D1,0603,1,LED-B,
"D2, D9",0603,2,LED-G,
"D3, D4, D5, D6, D7, D8",0603,6,LED-R,
"J1, J2",PinHeader_1x03_P1.27mm_Vertical,2,Conn_01x03_Pin,
"L1, L2, L3",L_Changjiang_FNR3015S,3,2.2uH,
"LED1, LED2, LED3, LED4, LED5, LED6, LED7, LED8",LED-SMD_4P-L2.0-W2.0-TL_WS2812B-2020,8,WS2812B-2020,
R1,0603,1,130kΩ,
"R10, R11, R12, R13, R14, R19, R20, R25, R26, R8, R9",0603,11,2kΩ,
"R15, R16, R17, R18",0603,4,47kΩ,
R2,0603,1,470kΩ,
"R21, R22, R23, R24",0603,4,5.1kΩ,
"R27, R28, R29, R7",0603,4,10kΩ,
R3,0603,1,680kΩ,
"R4, R5, R6",0603,3,150kΩ,
"SW1, SW2, SW3",SW-SMD_D-SWITCH_DS-THAM04-ABB-R,3,DS-THAM04-ABB-R,
U1,QFN-88_L10.0-W10.0-P0.40-BL-EP6.75,1,F1C200S,
U2,WQFN-20_L3.0-W3.0-P0.40-BL-EP,1,EA3036C,
U3,SOT-23-3_L3.0-W1.7-P0.95-LS2.9-BR,1,XC6206P302MR_C347375,
U4,MSOP-10_3x3mm_P0.5mm,1,CH340E,
U5,SOIC-8_L5.3-W5.3-P1.27-LS8.0-BL,1,W25Q128JVSIQTR,
U6,mpcie-full-card,1,MPCIE-Socket,
"USB1, USB2",USB-C-SMD_TYPE-C-6PIN-2MD-073,2,TYPE-C_16PIN_2MD(073),
X1,CRYSTAL-SMD_4P-L3.2-W2.5-BL,1,SMD-3225_4P_24.000MHZ_18PF,

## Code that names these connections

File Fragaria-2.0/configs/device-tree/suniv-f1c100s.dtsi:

// SPDX-License-Identifier: (GPL-2.0+ OR X11)
/*
 * Copyright 2018 Icenowy Zheng <icenowy@aosc.io>
 */

#include <dt-bindings/clock/suniv-ccu-f1c100s.h>
#include <dt-bindings/reset/suniv-ccu-f1c100s.h>

/ {
	#address-cells = <1>;
	#size-cells = <1>;
	interrupt-parent = <&intc>;

	clocks {
		#address-cells = <1>;
		#size-cells = <1>;
		ranges;

		osc24M: clk-24M {
			#clock-cells = <0>;
			compatible = "fixed-clock";
			clock-frequency = <24000000>;
			clock-output-names = "osc24M";
		};

		osc32k: clk-32k {
			#clock-cells = <0>;
			compatible = "fixed-clock";
			clock-frequency = <32768>;
			clock-output-names = "osc32k";
		};

		fake100M: clk-100M {
			#clock-cells = <0>;
			compatible = "fixed-clock";
			clock-frequency = <100000000>;
			clock-output-names = "fake-100M";
		};
	};

	cpus {
		#address-cells = <0>;
		#size-cells = <0>;

		cpu {
			compatible = "arm,arm926ej-s";
			device_type = "cpu";
		};
	};

	soc {
		compatible = "simple-bus";
		#address-cells = <1>;
		#size-cells = <1>;
		ranges;

		sram-controller@1c00000 {
			compatible = "allwinner,suniv-f1c100s-system-controller";
			reg = <0x01c00000 0x30>;
			#address-cells = <1>;
			#size-cells = <1>;
			ranges;

			sram_d: sram@10000 {
				compatible = "mmio-sram";
				reg = <0x00010000 0x1000>;
				#address-cells = <1>;
				#size-cells = <1>;
				ranges = <0 0x00010000 0x1000>;

				otg_sram: sram-section@0 {
					compatible = "allwinner,suniv-f1c100s-sram-d";
					reg = <0x0000 0x1000>;
					status = "disabled";
				};
			};
		};

		spi0: spi@1c05000 {
			compatible = "allwinner,suniv-spi",
				     "allwinner,suniv-f1c100s-spi";
			reg = <0x01c05000 0x1000>;
			interrupts = <10>;
			clocks = <&ccu CLK_BUS_SPI0>, <&ccu CLK_BUS_SPI0>;
			clock-names = "ahb", "mod";
			resets = <&ccu RST_BUS_SPI0>;
			status = "disabled";
			#address-cells = <1>;
			#size-cells = <0>;
		};

		ccu: clock@1c20000 {
			compatible = "allwinner,suniv-f1c100s-ccu";
			reg = <0x01c20000 0x400>;
			clocks = <&osc24M>, <&osc32k>;
			clock-names = "hosc", "losc";
			#clock-cells = <1>;
			#reset-cells = <1>;
		};

		intc: interrupt-controller@1c20400 {
			compatible = "allwinner,suniv-f1c100s-ic";
			reg = <0x01c20400 0x400>;
			interrupt-controller;
			#interrupt-cells = <1>;
		};

		pio: pinctrl@1c20800 {
			compatible = "allwinner,suniv-f1c100s-pinctrl";
			reg = <0x01c20800 0x400>;
			interrupts = <38>, <39>, <40>;
			clocks = <&ccu CLK_BUS_PIO>, <&osc24M>, <&osc32k>;
			clock-names = "apb", "hosc", "losc";
			gpio-controller;
			interrupt-controller;
			#interrupt-cells = <3>;
			#gpio-cells = <3>;

			spi0_pins_a: spi0-pins-pc {
				pins = "PC0", "PC1", "PC2", "PC3";
				function = "spi0";
			};

			mmc0_pins: mmc0-pins {
                pins = "PF0", "PF1", "PF2", "PF3", "PF4", "PF5";
                function = "mmc0";
            };

			uart2_pins_a: uart-pins-pe {
				pins = "PE8", "PE7";
				function = "uart2";
			};
		};

		timer@1c20c00 {
			compatible = "allwinner,suniv-f1c100s-timer";
			reg = <0x01c20c00 0x90>;
			interrupts = <13>;
			clocks = <&osc24M>;
		};

		wdt: watchdog@1c20ca0 {
			compatible = "allwinner,suniv-f1c100s-wdt";
			reg = <0x01c20ca0 0x20>;
			interrupts = <16>;
			clocks = <&osc32k>;
		};

		uart0: serial@1c25000 {
			compatible = "snps,dw-apb-uart";
			reg = <0x01c25000 0x400>;
			interrupts = <1>;
			reg-shift = <2>;
			reg-io-width = <4>;
			clocks = <&ccu CLK_BUS_UART0>;
			resets = <&ccu RST_BUS_UART0>;
			status = "disabled";
		};

		uart1: serial@1c25400 {
			compatible = "snps,dw-apb-uart";
			reg = <0x01c25400 0x400>;
			interrupts = <2>;
			reg-shift = <2>;
			reg-io-width = <4>;
			clocks = <&ccu CLK_BUS_UART1>;
			resets = <&ccu RST_BUS_UART1>;
			status = "disabled";
		};

		uart2: serial@1c25800 {
			compatible = "snps,dw-apb-uart";
			reg = <0x01c25800 0x400>;
			interrupts = <3>;
			reg-shift = <2>;
			reg-io-width = <4>;
			clocks = <&ccu CLK_BUS_UART2>;
			resets = <&ccu RST_BUS_UART2>;
			status = "disabled";
		};

		usb_otg: usb@1c13000 {
			compatible = "allwinner,suniv-musb";
			reg = <0x01c13000 0x0400>;
			clocks = <&ccu CLK_BUS_OTG>;
			resets = <&ccu RST_BUS_OTG>;
			interrupts = <26>;
			interrupt-names = "mc";
			phys = <&usbphy 0>;
			phy-names = "usb";
			extcon = <&usbphy 0>;
			allwinner,sram = <&otg_sram 1>;
			status = "disabled";
		};

		usbphy: phy@1c13400 {
			compatible = "allwinner,suniv-usb-phy";
			reg = <0x01c13400 0x10>;
			reg-names = "phy_ctrl";
			clocks = <&ccu CLK_USB_PHY0>;
			clock-names = "usb0_phy";
			resets = <&ccu RST_USB_PHY0>;
			reset-names = "usb0_reset";
			#phy-cells = <1>;
			status = "disabled";
		};

		mmc0: mmc@1c0f000 {
            compatible = "allwinner,suniv-f1c100s-mmc",
                     "allwinner,sun7i-a20-mmc";
            reg = <0x01c0f000 0x1000>;
            clocks = <&ccu CLK_BUS_MMC0>,
                 <&ccu CLK_MMC0>,
                 <&ccu CLK_MMC0_OUTPUT>,
                 <&ccu CLK_MMC0_SAMPLE>;
            clock-names = "ahb",
                          "mmc",
                          "output",
                          "sample";
            resets = <&ccu RST_BUS_MMC0>;
            reset-names = "ahb";
            interrupts = <23>;
            pinctrl-names = "default";
            pinctrl-0 = <&mmc0_pins>;
            status = "disabled";
            #address-cells = <1>;
            #size-cells = <0>;
        };
	};
};

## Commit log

2023-08-28 add doc
2023-08-29 init repo
2023-08-30 finish schemtic except soc
2023-09-01 finish core schematic
2023-09-05 finish layout'
2023-09-05 production ready
2023-09-07 minor update for production
2023-10-10 minor bug fix
2023-10-22 update test version
2023-10-22 add production file
2023-10-22 finish fragaria 2.0 core board
2023-10-25 finish extend board
2023-10-25 update library
2023-10-25 Align numbering specifications
2023-11-09 add gitignore
2023-11-09 add config files for constructing system
2023-11-16 export pdf
